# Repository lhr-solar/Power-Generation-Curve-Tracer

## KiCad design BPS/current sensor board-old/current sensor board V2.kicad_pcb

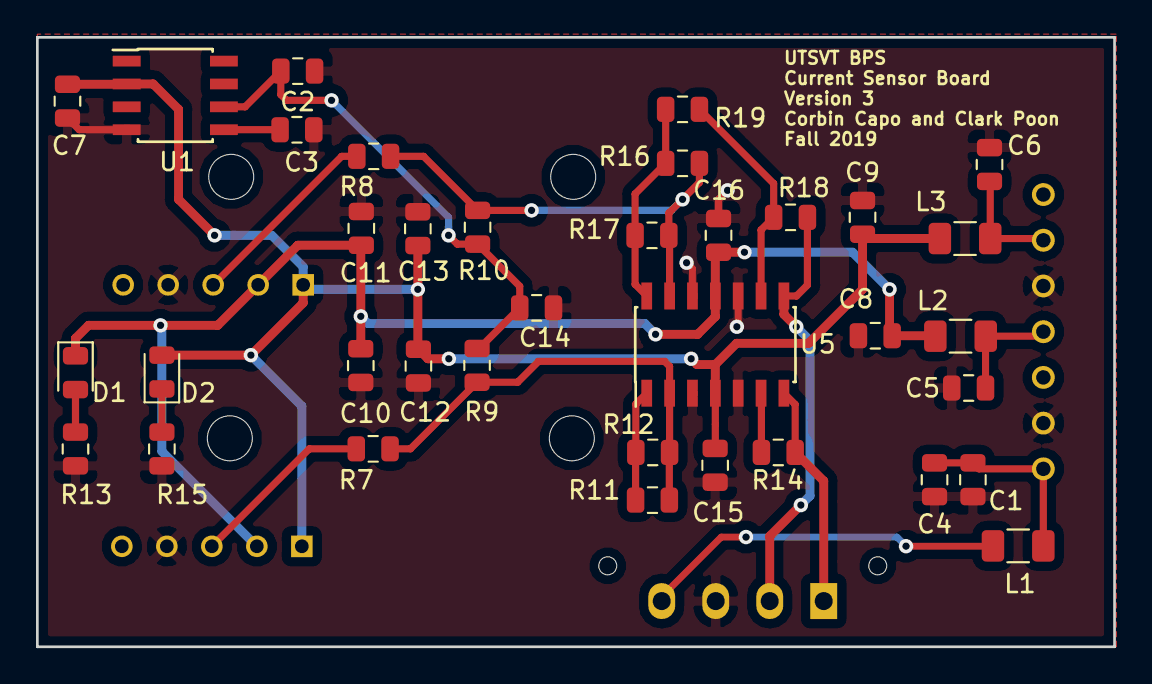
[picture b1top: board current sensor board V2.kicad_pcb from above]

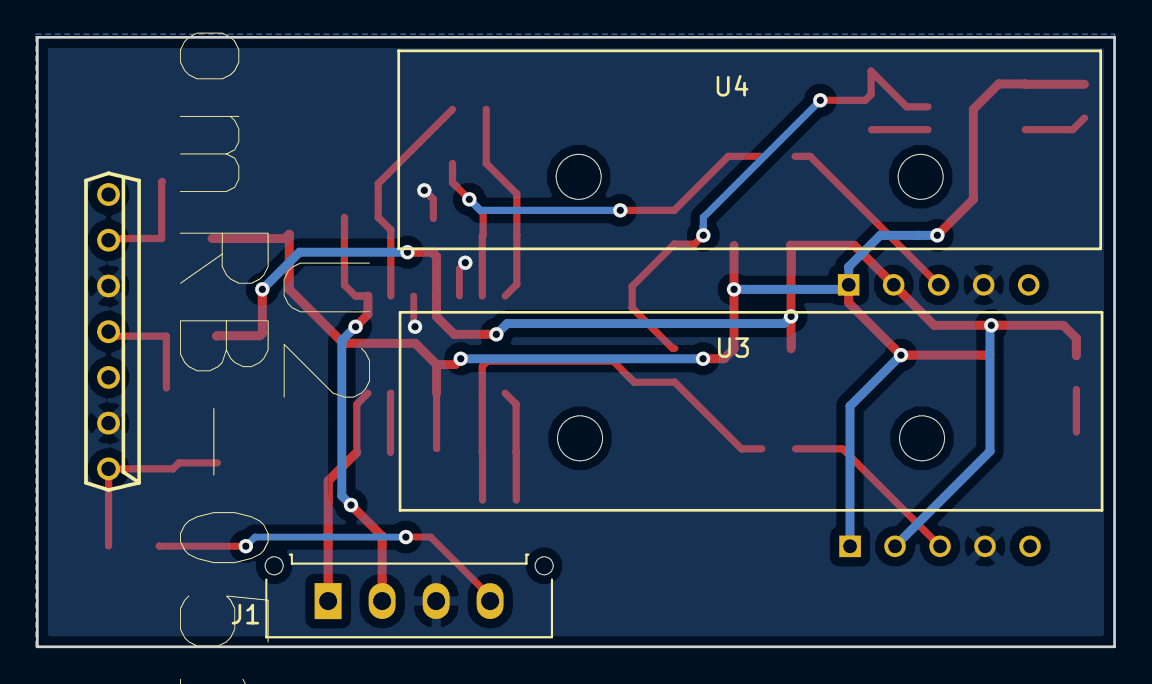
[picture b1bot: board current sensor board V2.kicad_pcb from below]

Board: 2 copper layers, 59.8 x 33.9 mm, 40 parts (4 on the bottom side), 21 nets.

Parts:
C1, C8, C9: 22 uF; C_0805_2012Metric
C2, C3, C4, C5, C6, C7, C10, C11, C12, C13, C14, C15, C16: 1 uF; C_0805_2012Metric
D1, D2: LED_Small; LED_0805_2012Metric
J1: Connector_Generic:Conn_01x04; Molex_Micro-Fit_3.0_43650-0415_1x04_P3.00mm_Vertical
L1, L2, L3: FB; L_1206_3216Metric
R7, R8, R9, R10, R11, R12, R14, R16, R17, R18, R19: 10 kOhm; R_0805_2012Metric
R13, R15: 1 kOhm; R_0805_2012Metric
U1: REF5040; SOIC-8_3.9x4.9mm_P1.27mm
U2: RecomRB-0515D; SIP7-P-2.54
U3: L08P50; L08PxxxD15
U4: L08P100; L08PxxxD15
U5: OPA4234U; SOIC-14_3.9x8.7mm_P1.27mm

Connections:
+5V: J1.4, L1.1
+15V: C7.1, C9.1, C12.1, C13.1, C15.1, D2.2, L3.2, U1.2, U3.1, U4.1, U5.4
-15V: C8.2, C10.1, C11.1, C16.1, D1.1, L2.2, U3.2, U4.2, U5.11
/HIGH_OUT: J1.2, R18.1, U5.8
/LOW_OUT: J1.1, R14.1, U5.7
/offset: C2.1, C14.1, R9.2, R10.1, U1.6
GND: C1.2, C2.2, C3.2, C4.2, C5.2, C6.1, C7.2, C8.1, C9.2, C10.2, C11.2, C12.2, C13.2, C14.2, C15.2, C16.2, J1.3, R13.2, R15.2, U1.4, U2.2, U2.5, U3.4, U4.4, U5.3, U5.5, U5.10, U5.12
unnamed: C1.1, C4.1, L1.2, U2.1
unnamed: C3.1, U1.5
unnamed: C5.1, L2.1, U2.4
unnamed: C6.2, L3.1, U2.6
unnamed: D1.2, R13.1
unnamed: D2.1, R15.1
unnamed: R7.2, U3.3
unnamed: R8.2, U4.3
unnamed: R8.1, R10.2, R16.1, R17.1, U5.13
unnamed: R11.1, R12.1, U5.1
unnamed: R7.1, R9.1, R11.2, R12.2, U5.2
unnamed: R14.2, U5.6
unnamed: R16.2, R17.2, R19.2, U5.14
unnamed: R18.2, R19.1, U5.9

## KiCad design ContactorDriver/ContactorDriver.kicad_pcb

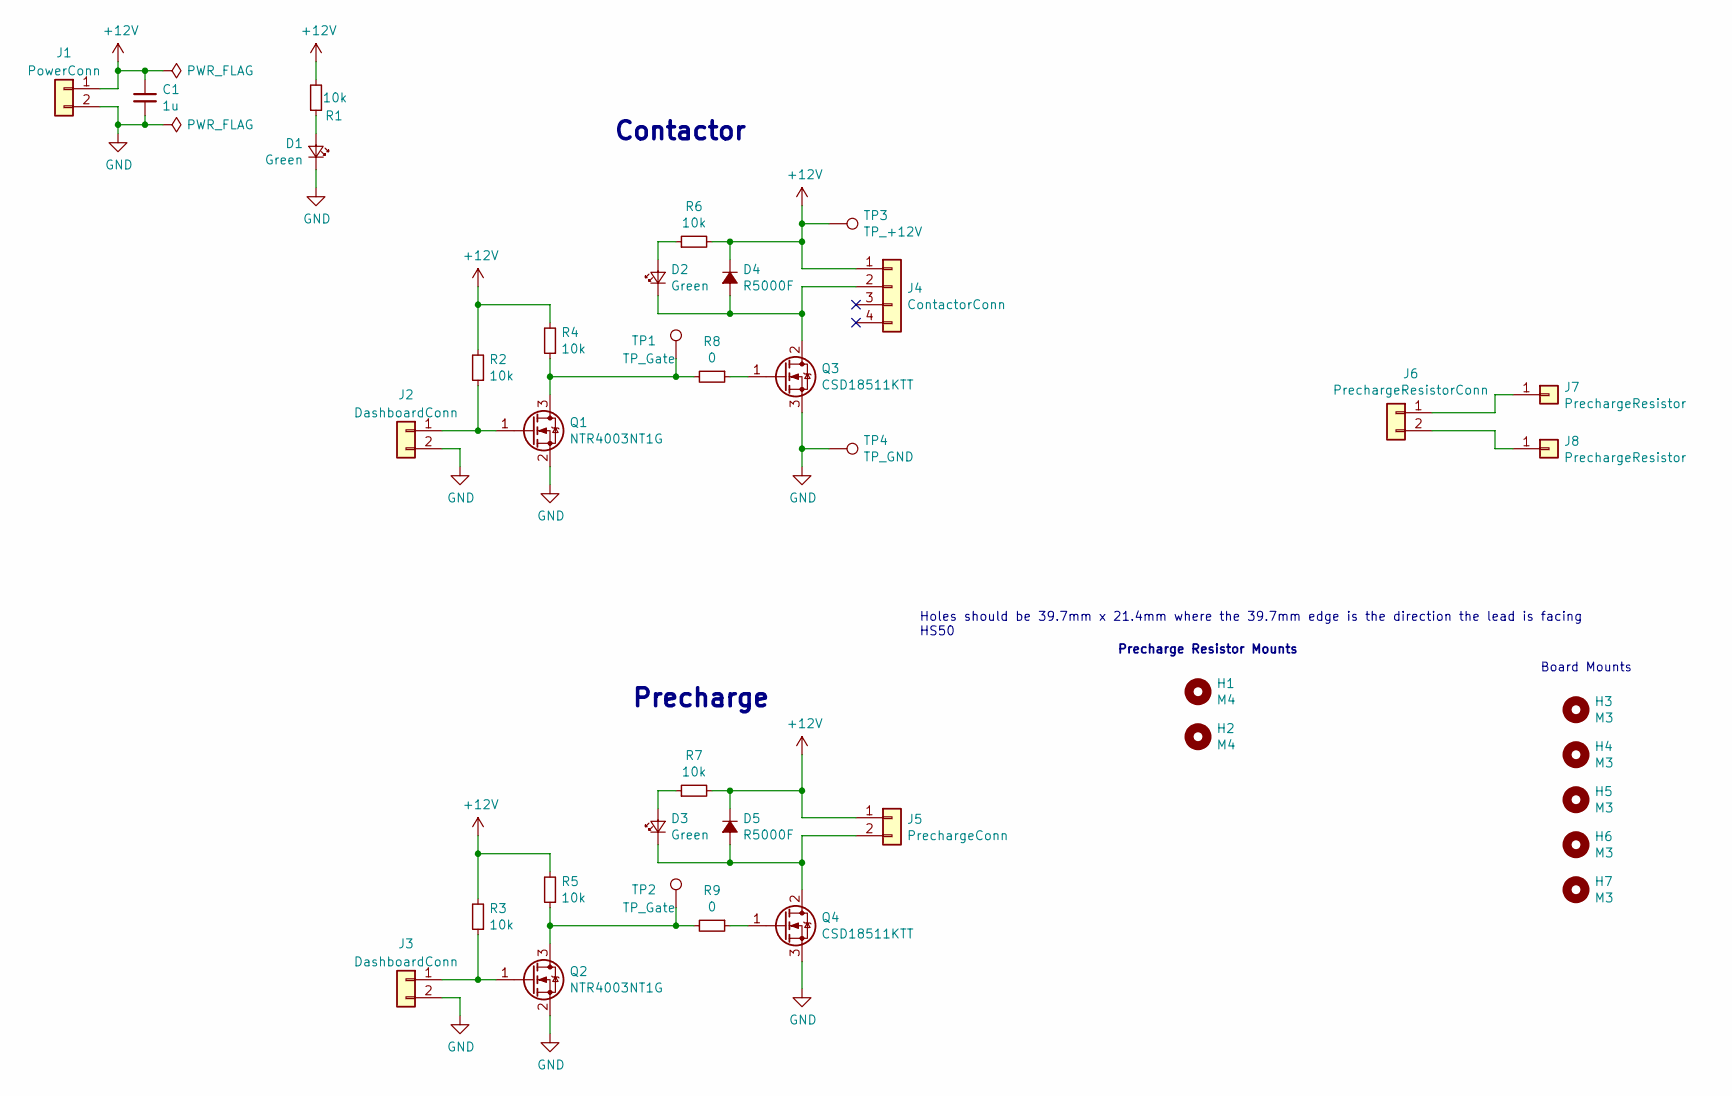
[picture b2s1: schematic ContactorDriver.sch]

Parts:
C1: 1u; C_0805_2012Metric_Pad1.15x1.40mm_HandSolder
D1, D2, D3: Green; LED_0805_2012Metric_Pad1.15x1.40mm_HandSolder
D4, D5: R5000F; D_DO-15_P10.16mm_Horizontal
H1, H2: M4; MountingHole_3.2mm_M3
H3, H4, H5, H6, H7: M3; MountingHole_3mm
J1: PowerConn; Molex_Micro-Fit_3.0_43650-0200_1x02_P3.00mm_Horizontal
J2, J3: DashboardConn; Molex_Micro-Fit_3.0_43650-0200_1x02_P3.00mm_Horizontal
J4: ContactorConn; Molex_Micro-Fit_3.0_43650-0415_1x04_P3.00mm_Vertical
J5: PrechargeConn; Molex_Micro-Fit_3.0_43650-0215_1x02_P3.00mm_Vertical
J6: PrechargeResistorConn; PhoenixContact_PowerCombicon5_GF_2x7.62mm
J7, J8: PrechargeResistor; SolderWirePad_1x01_Drill2mm
Q1, Q2: NTR4003NT1G; TSOT-23
Q3, Q4: CSD18511KTT; TO-263-3_TabPin2
R1, R2, R3, R4, R5, R6, R7: 10k; R_0805_2012Metric_Pad1.15x1.40mm_HandSolder
R8, R9: 0; R_0805_2012Metric_Pad1.15x1.40mm_HandSolder
TP1, TP2: TP_Gate; TestPoint_Keystone_5005-5009_Compact
TP3: TP_+12V; TestPoint_Keystone_5005-5009_Compact
TP4: TP_GND; TestPoint_Keystone_5005-5009_Compact

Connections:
+12V: C1.1, D4.1 (K), D5.1 (K), J1.1, J4.1, J5.1, R1.2, R2.2, R3.2, R4.2, R5.2, R6.2, R7.2, TP3.1
GND: C1.2, D1.1 (K), J1.2, J2.2, J3.2, Q1.2 (S), Q2.2 (S), Q3.3 (S), Q4.3 (S), TP4.1
unnamed: D1.2 (A), R1.1
unnamed: D2.1 (K), D4.2 (A), J4.2, Q3.2 (D)
unnamed: D2.2 (A), R6.1
unnamed: D3.1 (K), D5.2 (A), J5.2, Q4.2 (D)
unnamed: D3.2 (A), R7.1
unnamed: J2.1, Q1.1 (G), R2.1
unnamed: J3.1, Q2.1 (G), R3.1
unnamed: J6.1, J7.1
unnamed: J6.2, J8.1
unnamed: Q1.3 (D), R4.1, R8.2, TP1.1
unnamed: Q2.3 (D), R5.1, R9.2, TP2.1
unnamed: Q3.1 (G), R8.1
unnamed: Q4.1 (G), R9.1

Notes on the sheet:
Contactor
Precharge
Precharge Resistor Mounts
Board Mounts
Holes should be 39.7mm x 21.4mm where the 39.7mm edge is the direction the lead is facing HS50

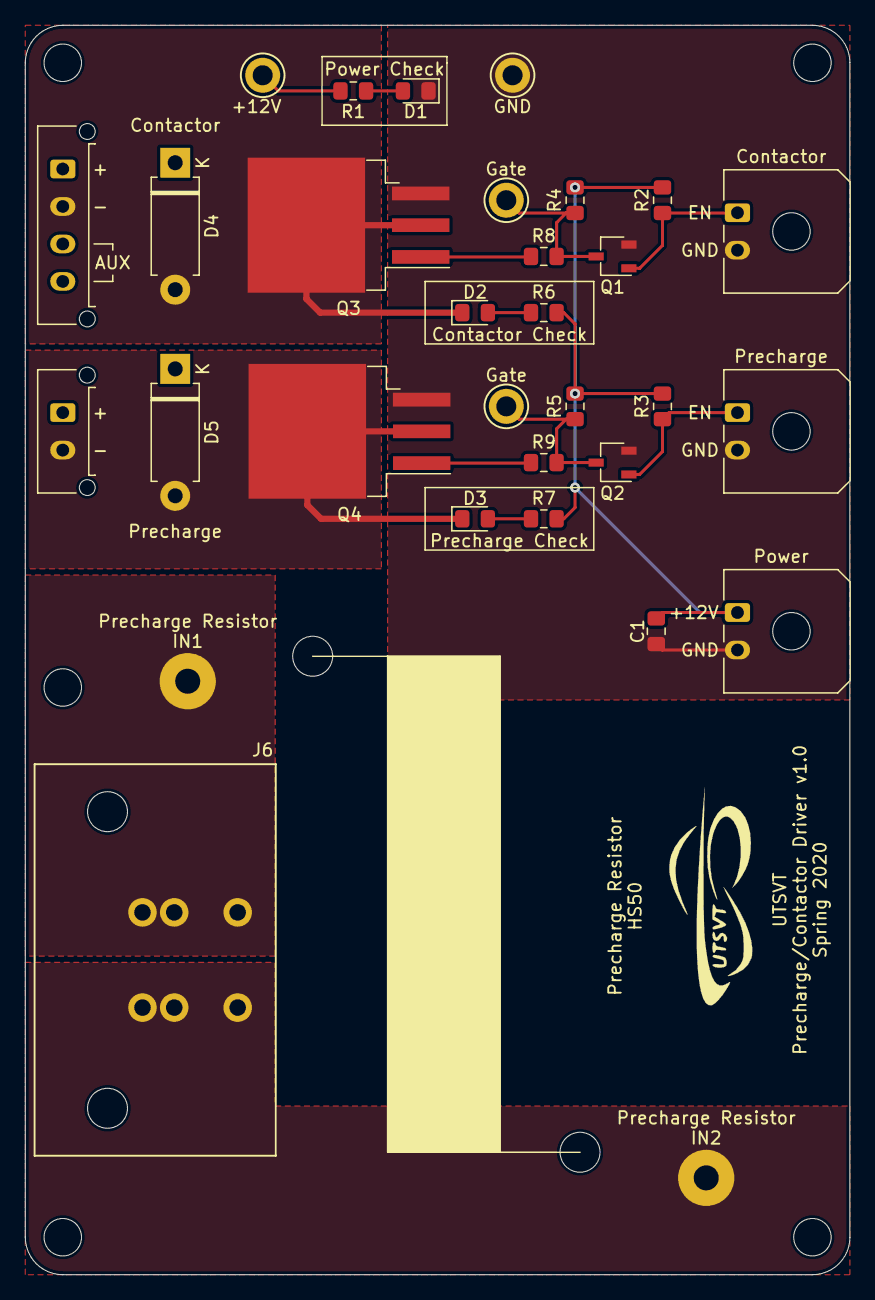
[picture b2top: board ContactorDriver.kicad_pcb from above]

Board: 2 copper layers, 66.0 x 100.0 mm, 38 parts (0 on the bottom side), 15 nets.

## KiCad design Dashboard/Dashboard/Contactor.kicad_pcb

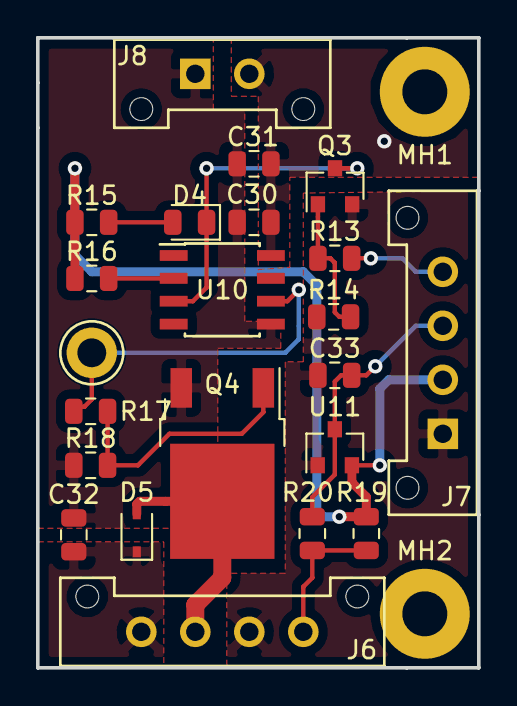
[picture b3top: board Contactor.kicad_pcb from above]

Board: 2 copper layers, 24.5 x 35.0 mm, 24 parts (0 on the bottom side), 14 nets.

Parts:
C30: 10uF; C_0805_2012Metric
C31: 0.1uF; C_0805_2012Metric
C32, C33: 1uF; C_0805_2012Metric
D4: ContactorEn; LED_0805_2012Metric
D5: 1N4148WS; D_SOD-323
J6: ContactorConnector; Molex_MicroFit3.0_1x4xP3.00mm_PolarizingPeg_Vertical
J7: Molex_MicroFit3.0_1x3xP3.00mm_PolarizingPeg_Verti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; Molex_MicroFit3.0_1x4xP3.00mm_PolarizingPeg_Vertical
J8: Molex_MicroFit3.0_1x2xP3.00mm_PolarizingPeg_Verti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; Molex_MicroFit3.0_1x2xP3.00mm_PolarizingPeg_Vertical
MH1, MH2: MountingHole_2.5mm_Pad
Q3: NVR4003NT3G; SOT-23
Q4: VND5N07-E; TO-252-2
R13, R17: 0; R_0805_2012Metric
R14, R18: 100k; R_0805_2012Metric
R15: 1.5k; R_0805_2012Metric
R16: 470; R_0805_2012Metric
R19: 4.7k; R_0805_2012Metric
R20: 1k; R_0805_2012Metric
TP13: ContactorGate_TP; TestPoint_Keystone_5005-5009_Compact
U10: SI8261ABC-IS; SOIC-8_3.9x4.9mm_P1.27mm
U11: BAS70-04; SOT-23

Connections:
+5V: J7.2, R15.1, R16.2, R19.2, U11.2
+12V: C30.1, C31.1, C32.2, D5.1, J6.1, J8.1, U10.8
/CONTACTOR_CHECK: C33.1, J7.3, R20.1, U11.3
/CONTACTOR_EN: J7.4, R13.2
/CONTACTOR_V-: D5.2, J6.2, Q4.2
GND: C33.2, J6.3, J7.1, Q3.2, R14.2, U11.1
GNDPWR: C30.2, C31.2, C32.1, J8.2, Q4.3, R18.2, U10.5
unnamed: D4.1, Q3.3, U10.3
unnamed: D4.2, R15.2
unnamed: J6.4, R19.1, R20.2
unnamed: Q3.1, R13.1, R14.1
unnamed: Q4.1, R17.1, R18.1
unnamed: R16.1, U10.2
unnamed: R17.2, TP13.1, U10.6

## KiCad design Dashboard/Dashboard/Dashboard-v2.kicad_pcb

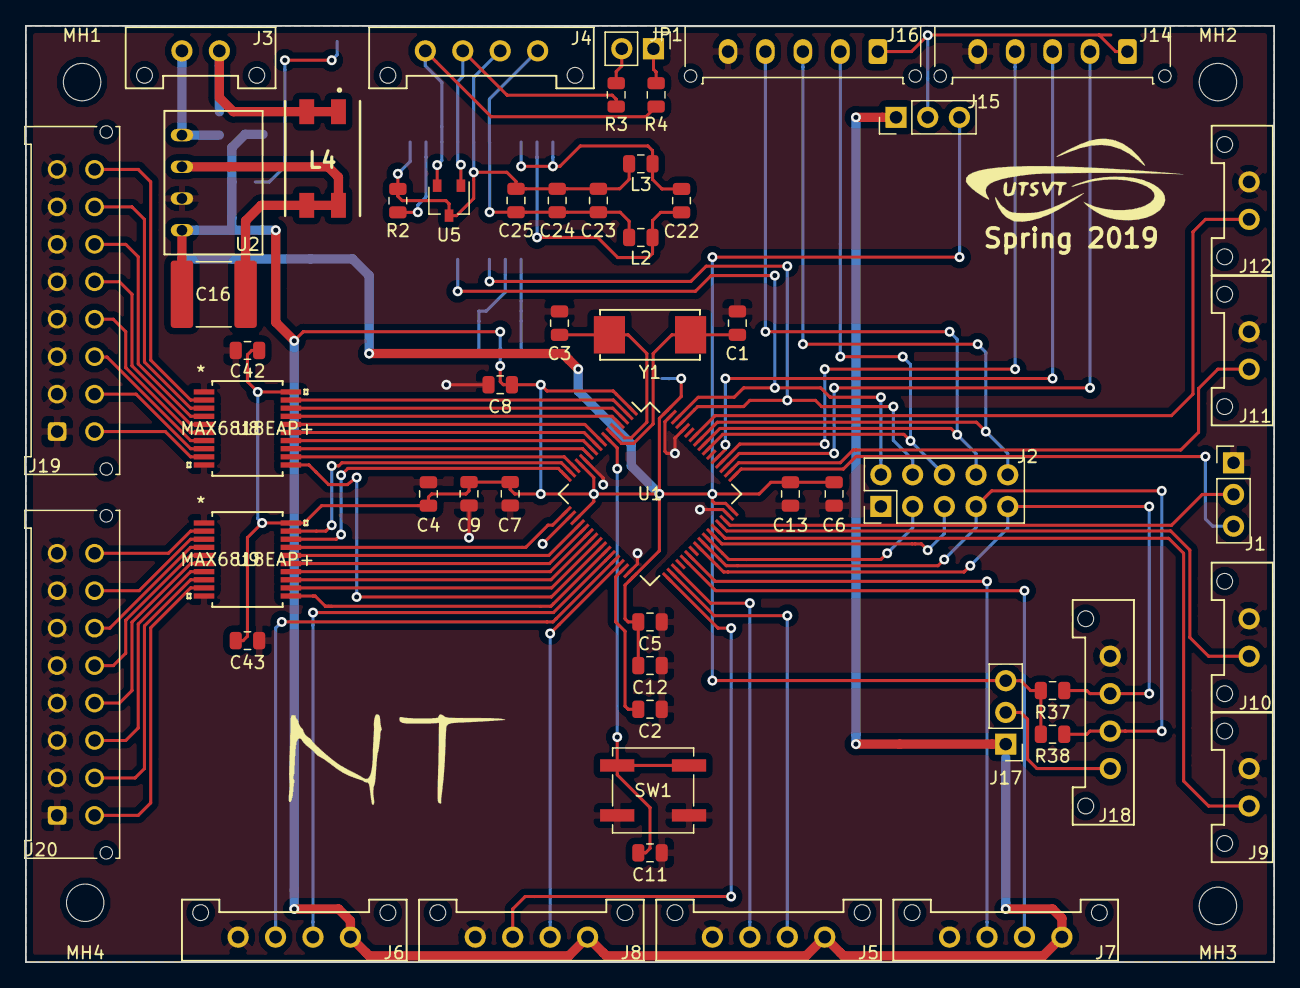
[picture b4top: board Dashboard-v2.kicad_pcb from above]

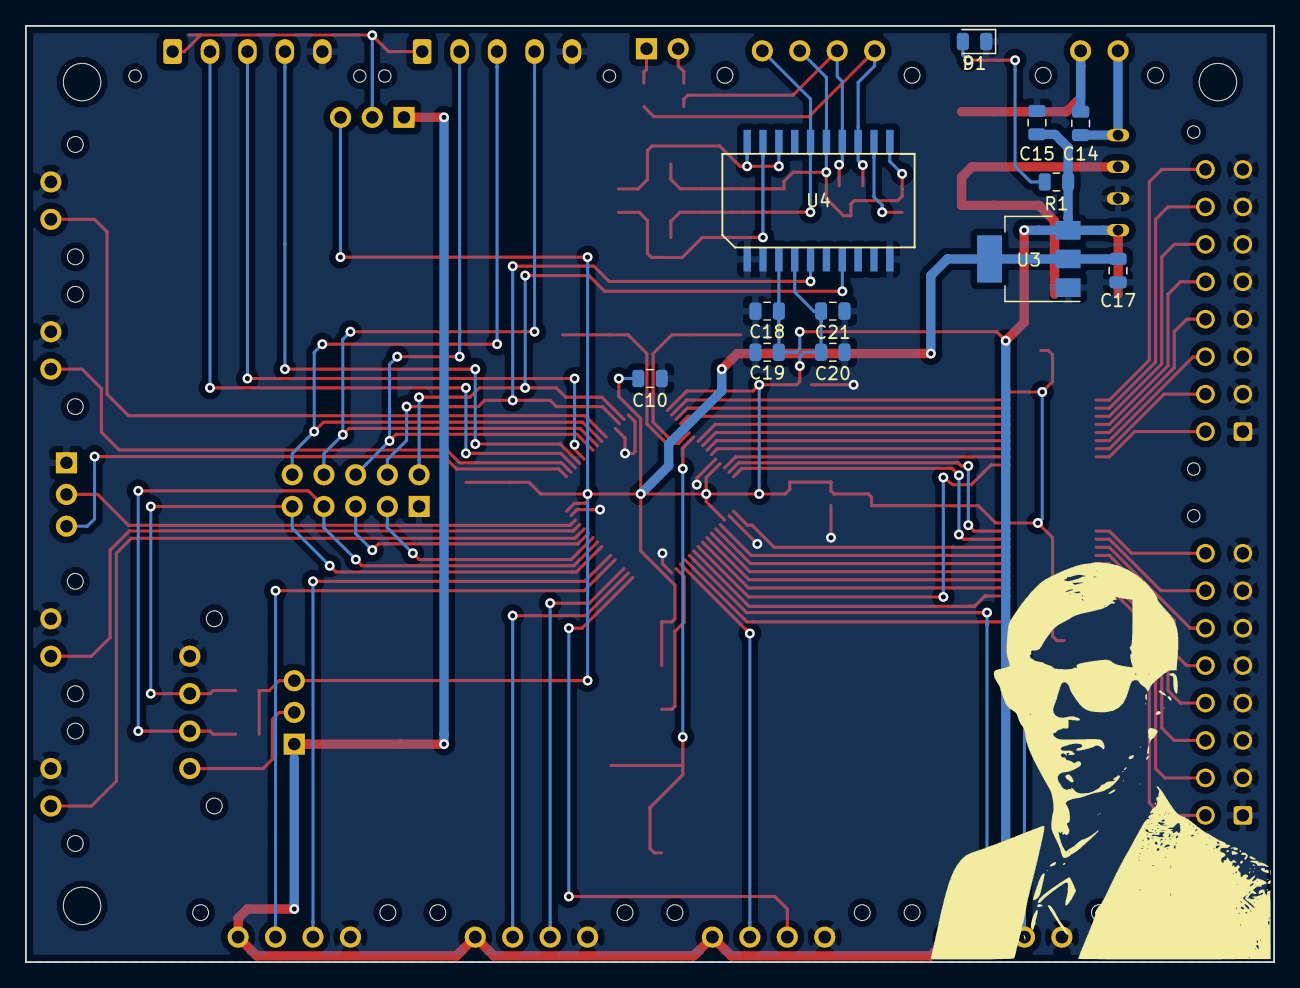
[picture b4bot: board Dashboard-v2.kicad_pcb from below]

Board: 2 copper layers, 100.0 x 75.0 mm, 70 parts (12 on the bottom side), 82 nets.

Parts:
C1, C3: 6pF; C_0805_2012Metric
C2: 2.2uF; C_0805_2012Metric
C4, C5, C6, C7, C8, C10, C11, C12, C15, C19, C20, C24: 0.1uF; C_0805_2012Metric
C9: 1uF; C_0805_2012Metric
C13, C14: 4.7uF; C_0805_2012Metric
C16: 470pF; C_2220_5650Metric
C17, C18, C22: 10uF; C_0805_2012Metric
C21, C25: 0.01uF; C_0805_2012Metric
C23: 0.22uF; C_0805_2012Metric
C42: .1uF; R_0805_2012Metric
C43: 0.1uF; R_0805_2012Metric
D1: PowerOn; LED_0805_2012Metric
J1: SWD; PinHeader_1x03_P2.54mm_Vertical
J2: Logic Analyzer; PinHeader_2x05_P2.54mm_Vertical
J3: CarPowerConnector; Molex_MicroFit3.0_1x2xP3.00mm_PolarizingPeg_Vertical
J4: CAN_Out; Molex_MicroFit3.0_1x4xP3.00mm_PolarizingPeg_Vertical
J5: Array Contactor 1; Molex_MicroFit3.0_1x4xP3.00mm_PolarizingPeg_Vertical
J6: Motor Contactor 1; Molex_MicroFit3.0_1x4xP3.00mm_PolarizingPeg_Vertical
J7: Array Contactor 2; Molex_MicroFit3.0_1x4xP3.00mm_PolarizingPeg_Vertical
J8: Motor Contactor 2; Molex_MicroFit3.0_1x4xP3.00mm_PolarizingPeg_Vertical
J9: Left Signal; Molex_MicroFit3.0_1x2xP3.00mm_PolarizingPeg_Vertical
J10: Right Signal; Molex_MicroFit3.0_1x2xP3.00mm_PolarizingPeg_Vertical
J11: Brake Signal; Molex_MicroFit3.0_1x2xP3.00mm_PolarizingPeg_Vertical
J12: Headlight; Molex_MicroFit3.0_1x2xP3.00mm_PolarizingPeg_Vertical
J14: SPI3; Molex_Micro-Fit_3.0_43650-0515_1x05_P3.00mm_Vertical
J15: Vs-SPI1; PinHeader_1x03_P2.54mm_Vertical
J16: SPI1; Molex_Micro-Fit_3.0_43650-0515_1x05_P3.00mm_Vertical
J17: Vs-I2C3; PinHeader_1x03_P2.54mm_Vertical
J18: I2C3; Molex_MicroFit3.0_1x4xP3.00mm_PolarizingPeg_Vertical
J19: Switches-1; Molex_Micro-Fit_3.0_43045-1612_2x08_P3.00mm_Vertical
J20: Switches-2; Molex_Micro-Fit_3.0_43045-1612_2x08_P3.00mm_Vertical
JP1: Termination Resistors; PinHeader_1x02_P2.54mm_Vertical
L2, L3: 2kH; L_0805_2012Metric
L4: SRF0905-100Y; SRF0905A
MH1, MH2, MH3, MH4: MountingHole; MountingHole_3mm
R1: 1.5k; R_0805_2012Metric
R2: 0; R_0805_2012Metric
R3, R4: 60; R_0805_2012Metric
R37, R38: 4.7k; R_0805_2012Metric
SW1: B3SL-1002P; SW_SPST_B3SL-1002P
U1: STM32F413RHTx; LQFP-64_10x10mm_P0.5mm
U2: RI3-1205S; RI3_DC_Converter
U3: NCP1117-3.3_SOT223; SOT-223-3_TabPin2
U4: ADM3055E; SOIC-20W_7.5x15.4mm_Pitch1.27mm
U5: CDSOT23-T24CAN; SOT-23W
U8, U9: MAX6818EAP+; MAX6818EAP&plus_
Y1: NX8045GB-8.000M-STD-CSJ-1

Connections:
+3V3: C4.1, C5.1, C6.1, C7.1, C8.1, C9.1, C10.1, C12.1, C13.1, C17.1, C20.1, C21.1, C42.1, C43.1, J15.3, J17.3, R37.1, R38.1, U1.1, U1.13, U1.19, U1.32, U1.48, U1.64, U3.2, U4.4, U8.20, U9.20
+5V: C15.1, C16.2, C18.1, C19.1, J5.4, J6.4, J7.4, J8.4, J15.1, J17.1, R1.1, U2.4, U3.3, U4.3
+12V: C14.1, J3.1, L4.1, L4.2
/AC1_CHECK: J5.2, U1.35
/AC1_EN: J5.3, U1.34
/AC2_CHECK: J7.2, U1.38
/AC2_EN: J7.3, U1.37
/Brake_Signal: J11.1, U1.50
/CAN1_RX: J2.4, U1.61, U4.5
/CAN1_TX: J2.2, U1.62, U4.7
/CAN/CAN_H: J4.3, R3.2, U4.14, U5.1
/CAN/CAN_L: J4.4, R4.2, U4.13, U5.2
/CAN/RSlope: R2.1, U4.12
/CAN/TERM_H: JP1.2, R3.1
/CAN/TERM_L: JP1.1, R4.1
/Headlight: J12.1, U1.58
/I2C3_SCL: J2.7, J18.2, R38.2, U1.41
/I2C3_SDA: J2.9, J18.3, R37.2, U1.40
/Left_Signal: J9.1, U1.44
/MC1_CHECK: J6.2, U1.28
/MC1_EN: J6.3, U1.27
/MC2_CHECK: J8.2, U1.33
/MC2_EN: J8.3, U1.29
/NRST: C11.1, SW1.1, U1.7
/OSC_IN: C3.1, U1.5, Y1.2
/OSC_OUT: C1.1, U1.6, Y1.1
/Right_Signal: J10.1, U1.45
/SPI1_CLK: J2.6, J16.2, U1.55
/SPI1_MISO: J2.8, J16.4, U1.56
/SPI1_MOSI: J2.10, J16.3, U1.57
/SPI3_CLK: J14.2, U1.51
/SPI3_MISO: J14.4, U1.52
/SPI3_MOSI: J14.3, U1.53
/SWCLK: J1.3, U1.49
/SWDIO: J1.2, U1.46
/Switches/arrayA: J20.14, U9.4
/Switches/bpsA: J20.16, U9.2
/Switches/brakesA: J19.12, U8.6
/Switches/cruiseA: J19.16, U8.2
/Switches/decreaseA: J19.13, U8.5
/Switches/hazardA: J20.12, U9.6
/Switches/increaseA: J19.14, U8.4
/Switches/leftA: J19.11, U8.7
/Switches/motorA: J20.15, U9.3
/Switches/regenA: J19.9, U8.9
/Switches/reverseA: J20.13, U9.5
/Switches/rightA: J19.10, U8.8
/Switches/set-cancelA: J19.15, U8.3
/Switches/xtra-switch1A: J20.11, U9.7
/Switches/xtra-switch2A: J20.10, U9.8
/Switches/xtra-switch3A: J20.9, U9.9
/UART1_RX: J2.5, U1.43
/UART1_TX: J2.3, U1.42
/array: U1.17, U9.17
/bps: U1.15, U9.19
/brake: U1.9, U8.15
/chan1: U1.25, U8.11
/chan2: U1.26, U9.11
/cruise: U1.2, U8.19
/decrease: U1.8, U8.16
/hazard: U1.21, U9.15
/increase: U1.4, U8.17
/left: U1.10, U8.14
/motor: U1.16, U9.18
/regen: U1.14, U8.12
/reverse: U1.20, U9.16
/right: U1.11, U8.13
/set-cancel: U1.3, U8.18
/xtra1: U1.22, U9.14
/xtra2: U1.23, U9.13
/xtra3: U1.24, U9.12
GND: C1.2, C2.2, C3.2, C4.2, C5.2, C6.2, C7.2, C8.2, C9.2, C10.2, C11.2, C12.2, C13.2, C15.2, C17.2, C18.2, C19.2, C20.2, C21.2, C42.2, C43.2, D1.1, J1.1, J2.1, J5.1, J6.1, J7.1, J8.1, J9.2, J10.2, J11.2, J12.2, J14.5, J16.5, J18.4, J19.1, J19.2, J19.3, J19.4, J19.5, J19.6, J19.7, J19.8, J20.1, J20.2, J20.3, J20.4, J20.5, J20.6, J20.7, J20.8, SW1.2, U1.12, U1.18, U1.31, U1.47, U1.60, U1.63, U2.3, U3.1, U4.1, U4.2, U4.10, U8.1, U8.10, U9.1, U9.10
GNDPWR: C14.2, J3.2, U2.1
unnamed: C2.1, U1.30
unnamed: C16.1, L4.3, L4.4, U2.2
unnamed: C22.1, L2.2, U4.19
unnamed: C22.2, L3.2, U4.18, U4.20
unnamed: C23.1, C24.1, C25.1, J4.1, L2.1, U4.16
unnamed: C23.2, C24.2, C25.2, J4.2, L3.1, R2.2, U4.11, U4.15, U5.3
unnamed: D1.2, R1.2
unnamed: J14.1, J15.2, J16.1
unnamed: J17.2, J18.1

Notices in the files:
parts and their libraries:
Copyright 2016 Accelerated Designs. All rights reserved.
